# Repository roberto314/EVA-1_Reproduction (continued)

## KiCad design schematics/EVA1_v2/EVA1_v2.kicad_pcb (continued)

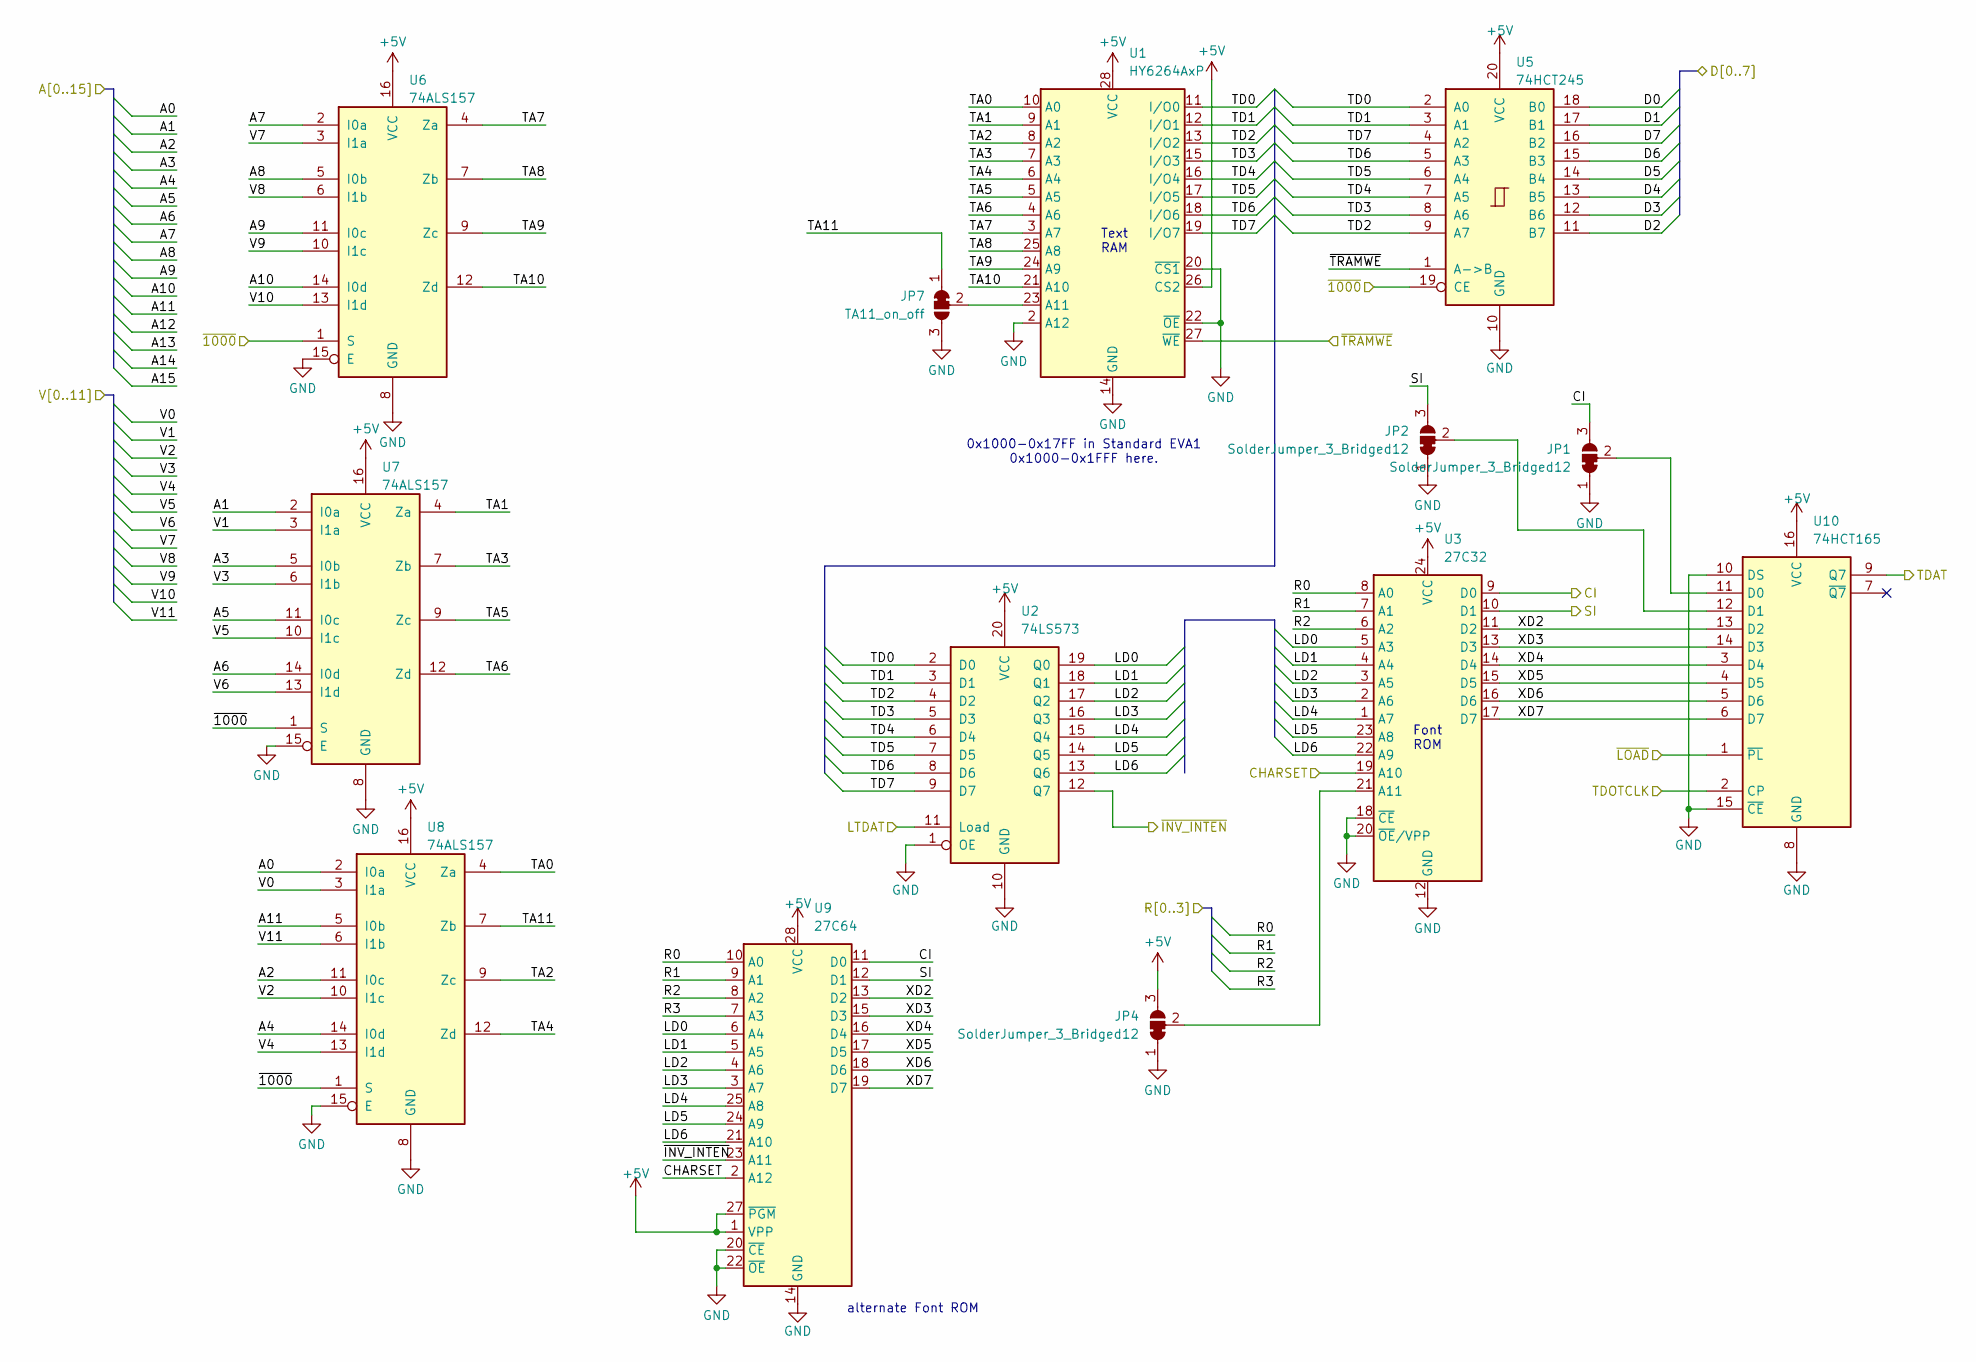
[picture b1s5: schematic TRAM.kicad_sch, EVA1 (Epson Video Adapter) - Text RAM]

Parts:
JP1, JP2, JP4: SolderJumper_3_Bridged12; SolderJumper-3_P1.3mm_Bridged12_RoundedPad1.0x1.5mm
JP7: TA11_on_off; SolderJumper-3_P1.3mm_Bridged12_RoundedPad1.0x1.5mm
U1: HY6264AxP; DIP-28_W15.24mm
U2: 74LS573; DIP-20_W7.62mm
U3: 27C32; DIP-24_W15.24mm
U5: 74HCT245; DIP-20_W7.62mm
U6, U7, U8: 74ALS157; DIP-16_W7.62mm
U9: 27C64; DIP-28_W15.24mm
U10: 74HCT165; DIP-16_W7.62mm_Socket

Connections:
+5V: JP4.3 (B), U1.26 (CS2), U1.28 (VCC), U2.20 (VCC), U3.24 (VCC), U5.20 (VCC), U6.16 (VCC), U7.16 (VCC), U8.16 (VCC), U9.1 (VPP), U9.27 (~PGM), U9.28 (VCC), U10.16 (VCC); also elsewhere on the board
/A0: U8.2 (I0a); also elsewhere on the board
/A1: U7.2 (I0a); also elsewhere on the board
/A2: U8.11 (I0c); also elsewhere on the board
/A3: U7.5 (I0b); also elsewhere on the board
/A4: U8.14 (I0d); also elsewhere on the board
/A5: U7.11 (I0c); also elsewhere on the board
/A6: U7.14 (I0d); also elsewhere on the board
/A7: U6.2 (I0a); also elsewhere on the board
/A8: U6.5 (I0b); also elsewhere on the board
/A9: U6.11 (I0c); also elsewhere on the board
/A10: U6.14 (I0d); also elsewhere on the board
/A11: U8.5 (I0b); also elsewhere on the board
/CHARSET: U3.19 (A10), U9.2 (A12); also elsewhere on the board
/CI: JP1.3 (B), U3.9 (D0), U9.11 (D0)
/D0: U5.18 (B0); also elsewhere on the board
/D1: U5.17 (B1); also elsewhere on the board
/D2: U5.11 (B7); also elsewhere on the board
/D3: U5.12 (B6); also elsewhere on the board
/D4: U5.13 (B5); also elsewhere on the board
/D5: U5.14 (B4); also elsewhere on the board
/D6: U5.15 (B3); also elsewhere on the board
/D7: U5.16 (B2); also elsewhere on the board
/LTDAT: U2.11 (Load); also elsewhere on the board
/R0: U3.8 (A0), U9.10 (A0); also elsewhere on the board
/R1: U3.7 (A1), U9.9 (A1); also elsewhere on the board
/R2: U3.6 (A2), U9.8 (A2); also elsewhere on the board
/R3: U9.7 (A3); also elsewhere on the board
/SI: JP2.3 (B), U3.10 (D1), U9.12 (D1)
/TDAT: U10.9 (Q7); also elsewhere on the board
/TDOTCLK: U10.2 (CP); also elsewhere on the board
/Text RAM, MUX and Shiftregister1/LD0: U2.19 (Q0), U3.5 (A3), U9.6 (A4)
/Text RAM, MUX and Shiftregister1/LD1: U2.18 (Q1), U3.4 (A4), U9.5 (A5)
/Text RAM, MUX and Shiftregister1/LD2: U2.17 (Q2), U3.3 (A5), U9.4 (A6)
/Text RAM, MUX and Shiftregister1/LD3: U2.16 (Q3), U3.2 (A6), U9.3 (A7)
/Text RAM, MUX and Shiftregister1/LD4: U2.15 (Q4), U3.1 (A7), U9.25 (A8)
/Text RAM, MUX and Shiftregister1/LD5: U2.14 (Q5), U3.23 (A8), U9.24 (A9)
/Text RAM, MUX and Shiftregister1/LD6: U2.13 (Q6), U3.22 (A9), U9.21 (A10)
/Text RAM, MUX and Shiftregister1/TA0: U1.10 (A0), U8.4 (Za)
/Text RAM, MUX and Shiftregister1/TA1: U1.9 (A1), U7.4 (Za)
/Text RAM, MUX and Shiftregister1/TA2: U1.8 (A2), U8.9 (Zc)
/Text RAM, MUX and Shiftregister1/TA3: U1.7 (A3), U7.7 (Zb)
/Text RAM, MUX and Shiftregister1/TA4: U1.6 (A4), U8.12 (Zd)
/Text RAM, MUX and Shiftregister1/TA5: U1.5 (A5), U7.9 (Zc)
/Text RAM, MUX and Shiftregister1/TA6: U1.4 (A6), U7.12 (Zd)
/Text RAM, MUX and Shiftregister1/TA7: U1.3 (A7), U6.4 (Za)
/Text RAM, MUX and Shiftregister1/TA8: U1.25 (A8), U6.7 (Zb)
/Text RAM, MUX and Shiftregister1/TA9: U1.24 (A9), U6.9 (Zc)
/Text RAM, MUX and Shiftregister1/TA10: U1.21 (A10), U6.12 (Zd)
/Text RAM, MUX and Shiftregister1/TA11: JP7.1 (A), U8.7 (Zb)
/Text RAM, MUX and Shiftregister1/TD0: U1.11 (I/O0), U2.2 (D0), U5.2 (A0)
/Text RAM, MUX and Shiftregister1/TD1: U1.12 (I/O1), U2.3 (D1), U5.3 (A1)
/Text RAM, MUX and Shiftregister1/TD2: U1.13 (I/O2), U2.4 (D2), U5.9 (A7)
/Text RAM, MUX and Shiftregister1/TD3: U1.15 (I/O3), U2.5 (D3), U5.8 (A6)
/Text RAM, MUX and Shiftregister1/TD4: U1.16 (I/O4), U2.6 (D4), U5.7 (A5)
/Text RAM, MUX and Shiftregister1/TD5: U1.17 (I/O5), U2.7 (D5), U5.6 (A4)
/Text RAM, MUX and Shiftregister1/TD6: U1.18 (I/O6), U2.8 (D6), U5.5 (A3)
/Text RAM, MUX and Shiftregister1/TD7: U1.19 (I/O7), U2.9 (D7), U5.4 (A2)
/Text RAM, MUX and Shiftregister1/XD2: U3.11 (D2), U9.13 (D2), U10.13 (D2)
/Text RAM, MUX and Shiftregister1/XD3: U3.13 (D3), U9.15 (D3), U10.14 (D3)
/Text RAM, MUX and Shiftregister1/XD4: U3.14 (D4), U9.16 (D4), U10.3 (D4)
/Text RAM, MUX and Shiftregister1/XD5: U3.15 (D5), U9.17 (D5), U10.4 (D5)
/Text RAM, MUX and Shiftregister1/XD6: U3.16 (D6), U9.18 (D6), U10.5 (D6)
/Text RAM, MUX and Shiftregister1/XD7: U3.17 (D7), U9.19 (D7), U10.6 (D7)
/Text RAM, MUX and Shiftregister1/~INV_INTEN: U2.12 (Q7), U9.23 (A11); also elsewhere on the board
/V0: U8.3 (I1a); also elsewhere on the board
/V1: U7.3 (I1a); also elsewhere on the board
/V2: U8.10 (I1c); also elsewhere on the board
/V3: U7.6 (I1b); also elsewhere on the board
/V4: U8.13 (I1d); also elsewhere on the board
/V5: U7.10 (I1c); also elsewhere on the board
/V6: U7.13 (I1d); also elsewhere on the board
/V7: U6.3 (I1a); also elsewhere on the board
/V8: U6.6 (I1b); also elsewhere on the board
/V9: U6.10 (I1c); also elsewhere on the board
/V10: U6.13 (I1d); also elsewhere on the board
/V11: U8.6 (I1b); also elsewhere on the board
/~1000: U5.19 (CE), U6.1 (S), U7.1 (S), U8.1 (S); also elsewhere on the board
/~LOAD: U10.1 (~PL); also elsewhere on the board
/~TRAMWE: U1.27 (~WE), U5.1 (A->B); also elsewhere on the board
GND: JP1.1 (A), JP2.1 (A), JP4.1 (A), JP7.3 (B), U1.2 (A12), U1.14 (GND), U1.20 (~CS1), U1.22 (~OE), U2.1 (OE), U2.10 (GND), U3.12 (GND), U3.18 (~CE), U3.20 (~OE/VPP), U5.10 (GND), U6.8 (GND), U6.15 (E), U7.8 (GND), U7.15 (E), U8.8 (GND), U8.15 (E), U9.14 (GND), U9.20 (~CE), U9.22 (~OE), U10.8 (GND), U10.10 (DS), U10.15 (~CE); also elsewhere on the board
unnamed: JP1.2 (C), U10.11 (D0)
unnamed: JP2.2 (C), U10.12 (D1)
unnamed: JP4.2 (C), U3.21 (A11)
unnamed: JP7.2 (C), U1.23 (A11)

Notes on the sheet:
0x1000-0x17FF in Standard EVA1 0x1000-0x1FFF here.
Font ROM
Text RAM
alternate Font ROM

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
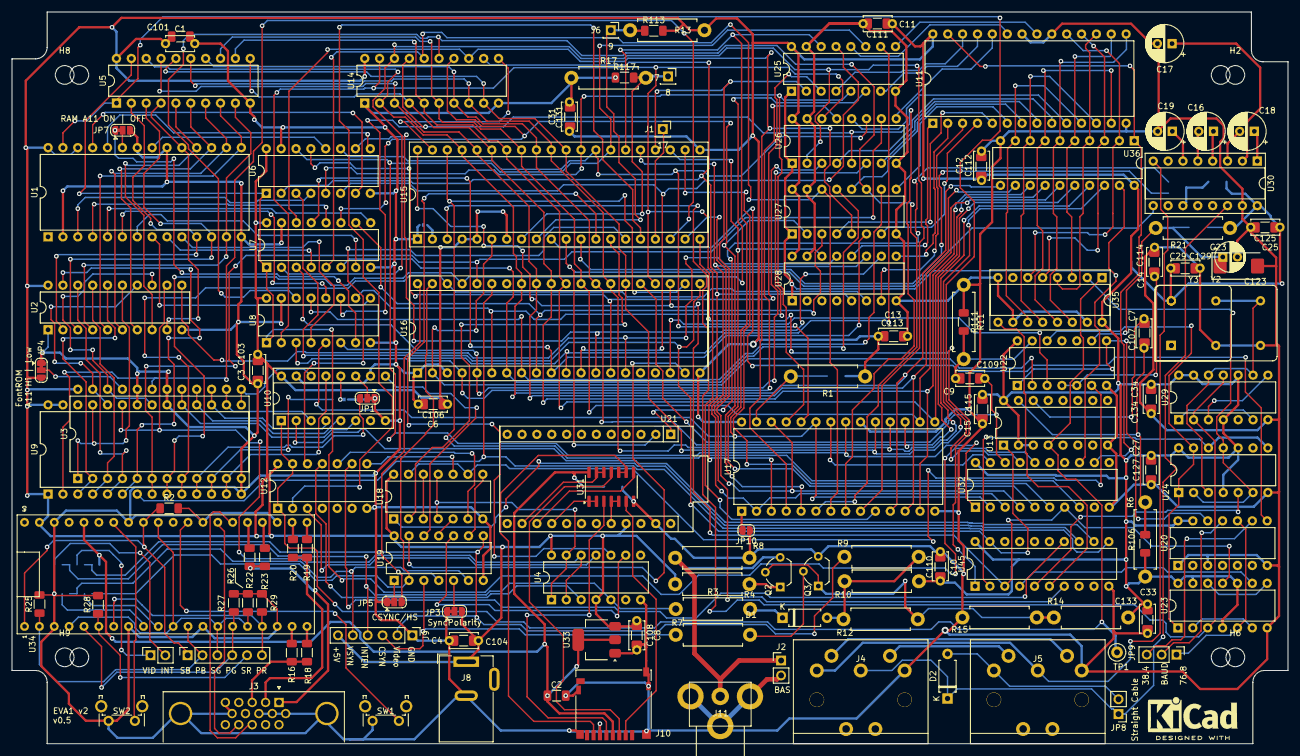
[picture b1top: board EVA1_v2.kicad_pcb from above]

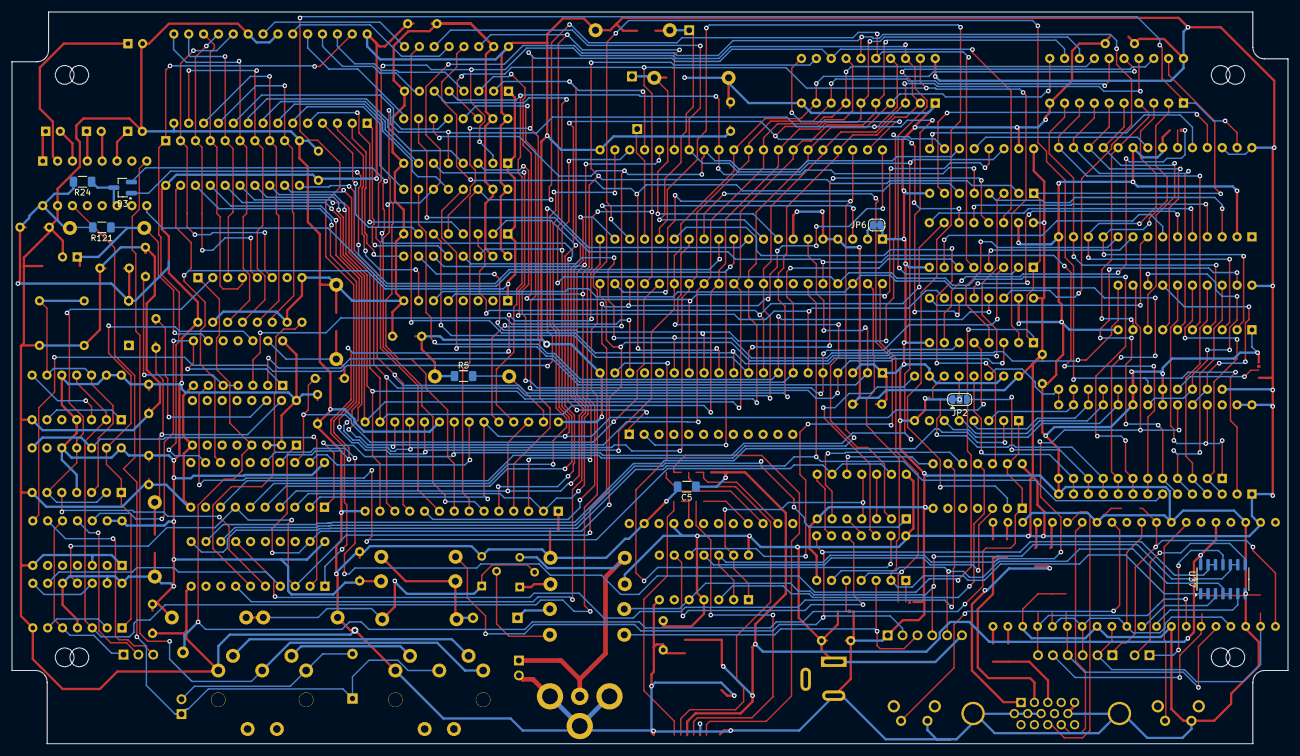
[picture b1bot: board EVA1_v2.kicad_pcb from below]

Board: 2 copper layers, 218.0 x 125.0 mm, 160 parts (8 on the bottom side), 229 nets.

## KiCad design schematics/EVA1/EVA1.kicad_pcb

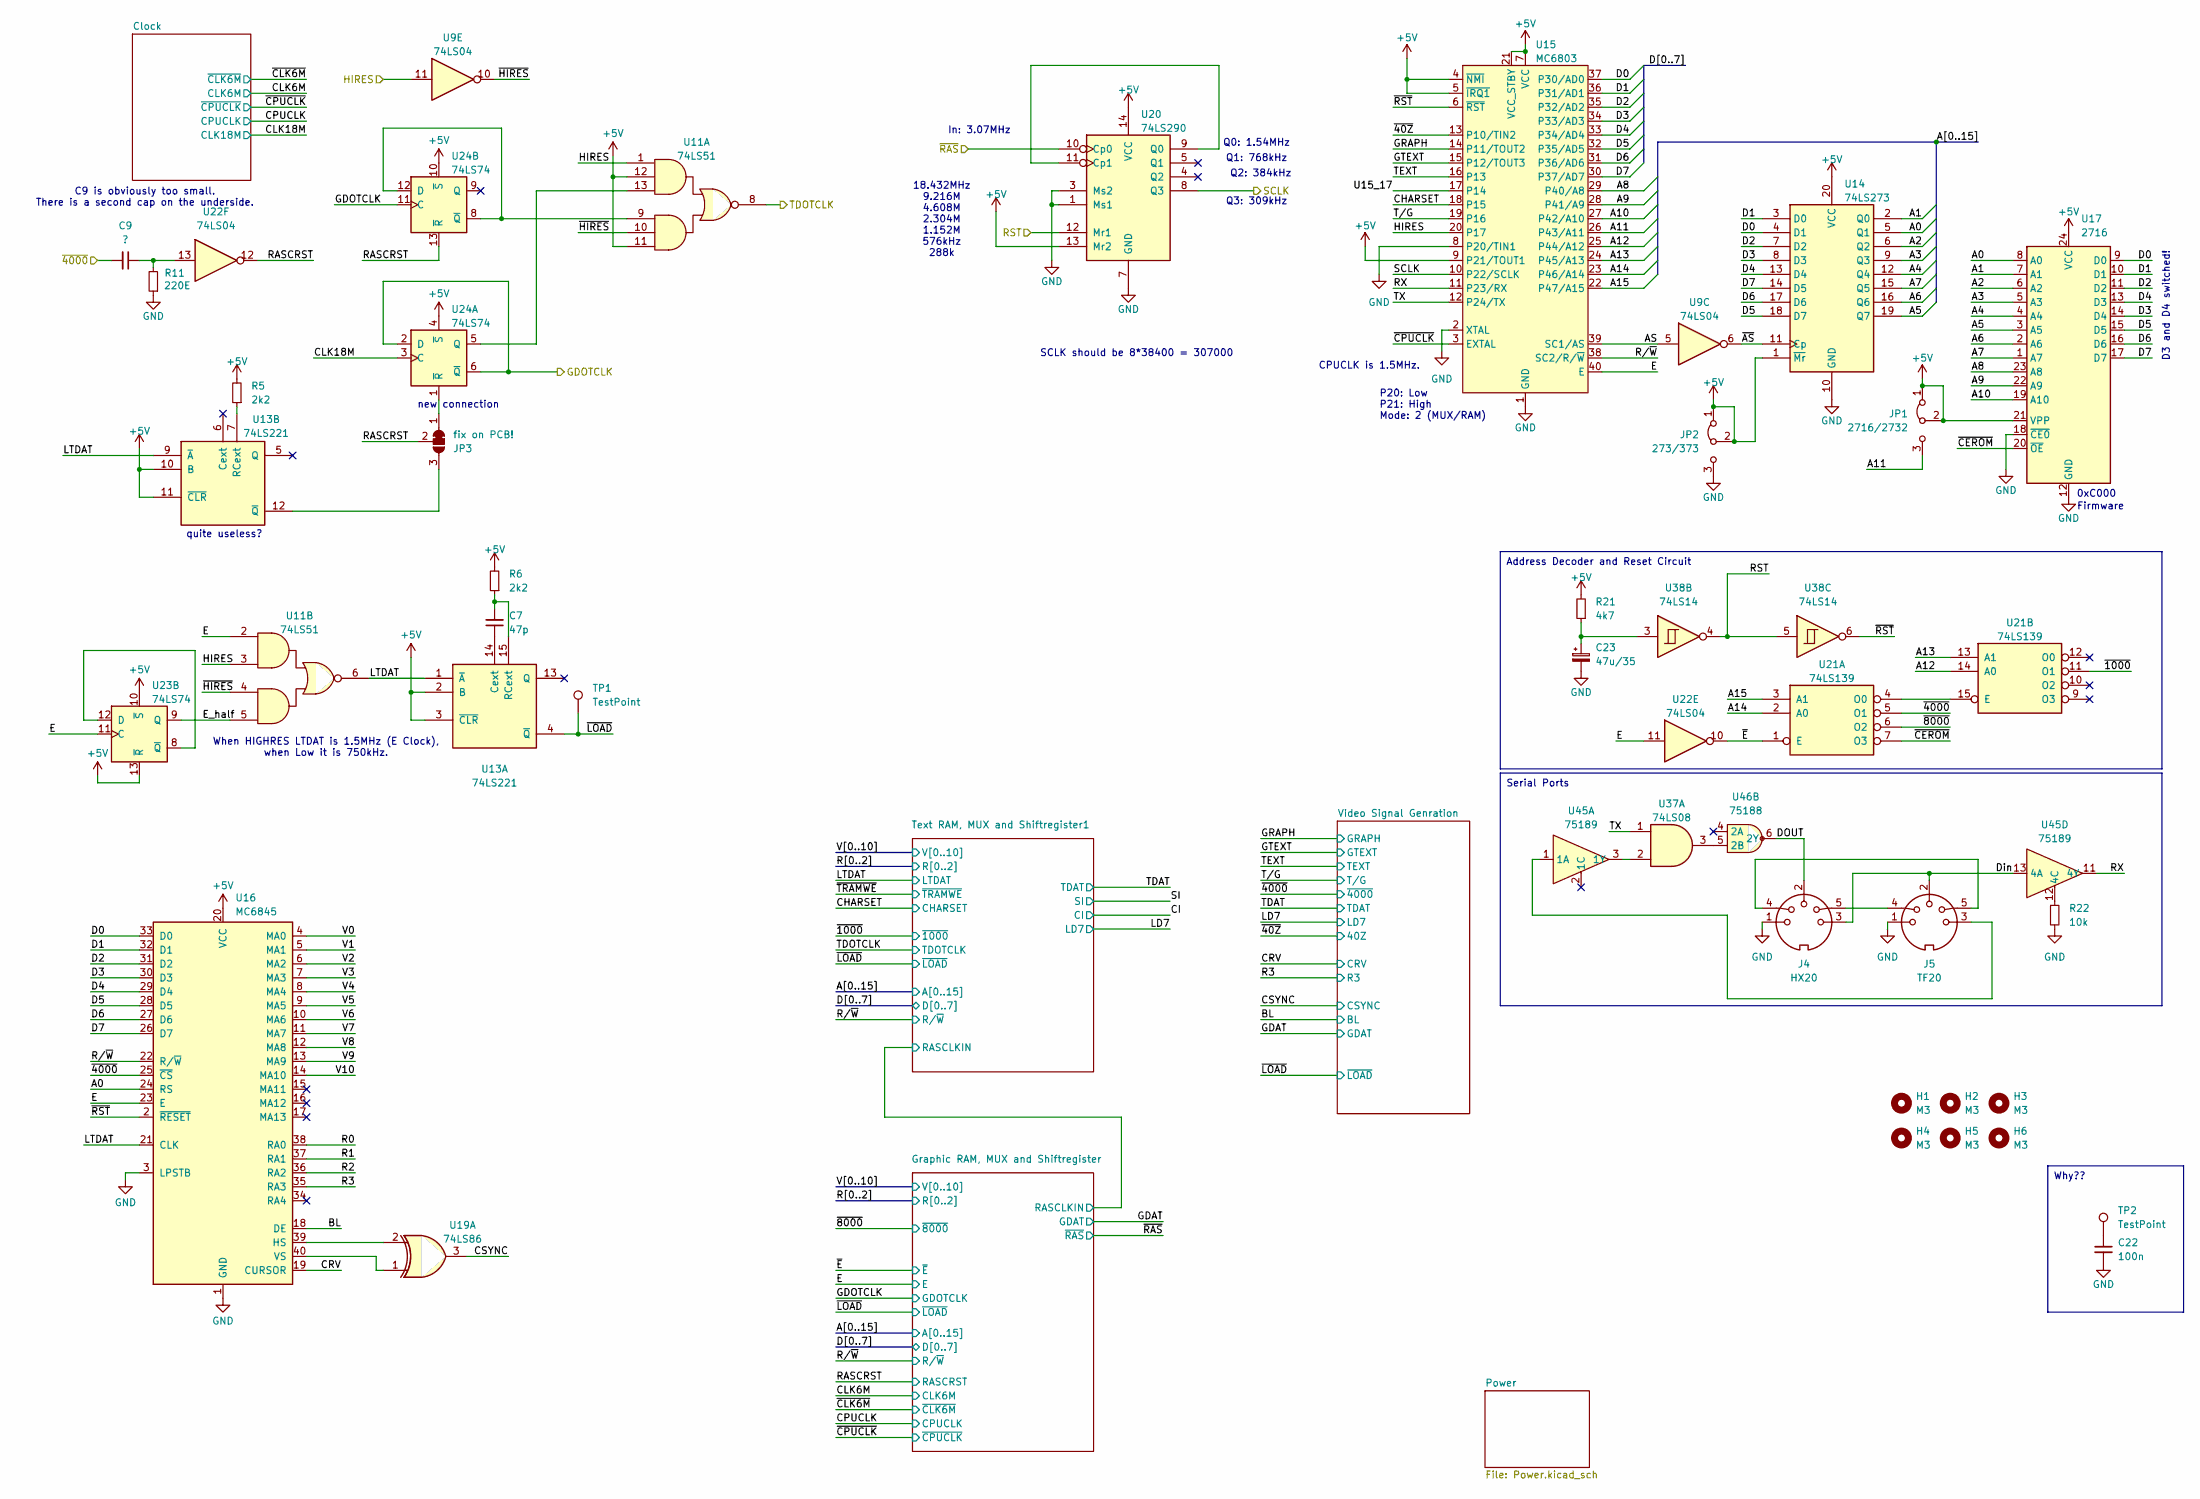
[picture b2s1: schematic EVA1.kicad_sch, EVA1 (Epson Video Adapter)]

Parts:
C7: 47p; C_Disc_D4.7mm_W2.5mm_P5.00mm
C9: ?; C_Disc_D4.7mm_W2.5mm_P5.00mm
C22: 100n; C_Disc_D4.7mm_W2.5mm_P5.00mm
C23: 47u/35; CP_Radial_D5.0mm_P2.50mm
H1, H2, H3, H4, H5, H6: M3; MountingHole_3.2mm_M3
J4: HX20; DIN-5_Stereo
J5: TF20; DIN-5_Stereo
JP1: 2716/2732; PinHeader_1x03_P2.54mm_Vertical
JP2: 273/373; PinHeader_1x03_P2.54mm_Vertical
JP3: fix on PCB!; SolderJumper-3_P1.3mm_Bridged12_RoundedPad1.0x1.5mm
R5, R6: 2k2; R_Axial_DIN0411_L9.9mm_D3.6mm_P12.70mm_Horizontal
R11: 220E; R_Axial_DIN0411_L9.9mm_D3.6mm_P12.70mm_Horizontal
R21: 4k7; R_Axial_DIN0411_L9.9mm_D3.6mm_P12.70mm_Horizontal
R22: 10k; R_Axial_DIN0411_L9.9mm_D3.6mm_P12.70mm_Horizontal
TP1, TP2: TestPoint; TestPoint_Loop_D1.80mm_Drill1.0mm_Beaded
U9, U22: 74LS04; DIP-14_W7.62mm
U11: 74LS51; DIP-14_W7.62mm
U13: 74LS221; DIP-16_W7.62mm
U14: 74LS273; DIP-20_W7.62mm
U15: MC6803; DIP-40_W15.24mm_Socket
U16: MC6845; DIP-40_W15.24mm_Socket
U17: 2716; DIP-24_W15.24mm
U19: 74LS86; DIP-14_W7.62mm
U20: 74LS290; DIP-14_W7.62mm
U21: 74LS139; DIP-16_W7.62mm
U23, U24: 74LS74; DIP-14_W7.62mm
U37: 74LS08; DIP-14_W7.62mm
U38: 74LS14; DIP-14_W7.62mm
U45: 75189; DIP-14_W7.62mm
U46: 75188; DIP-14_W7.62mm

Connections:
+5V: JP1.1 (A), JP1.2 (C), JP2.1 (A), JP2.2 (C), R5.2, R6.2, R21.2, U11.11, U11.12, U13.2 (B), U13.3 (~CLR), U13.10 (B), U13.11 (~CLR), U14.1 (~Mr), U14.20 (VCC), U15.4 (~NMI), U15.5 (~IRQ1), U15.7 (VCC), U15.9 (P21/TOUT1), U15.21 (VCC_STBY), U16.20 (VCC), U17.21 (VPP), U17.24 (VCC), U20.13 (Mr2), U20.14 (VCC), U23.10 (~S), U23.13 (~R), U24.4 (~S), U24.10 (~S); also elsewhere on the board
/A0: U14.5 (Q1), U16.24 (RS), U17.8 (A0); also elsewhere on the board
/A1: U14.2 (Q0), U17.7 (A1); also elsewhere on the board
/A2: U14.6 (Q2), U17.6 (A2); also elsewhere on the board
/A3: U14.9 (Q3), U17.5 (A3); also elsewhere on the board
/A4: U14.12 (Q4), U17.4 (A4); also elsewhere on the board
/A5: U14.19 (Q7), U17.3 (A5); also elsewhere on the board
/A6: U14.16 (Q6), U17.2 (A6); also elsewhere on the board
/A7: U14.15 (Q5), U17.1 (A7); also elsewhere on the board
/A8: U15.29 (P40/A8), U17.23 (A8); also elsewhere on the board
/A9: U15.28 (P41/A9), U17.22 (A9); also elsewhere on the board
/A10: U15.27 (P42/A10), U17.19 (A10); also elsewhere on the board
/A11: JP1.3 (B), U15.26 (P43/A11); also elsewhere on the board
/A12: U15.25 (P44/A12), U21.14 (A0); also elsewhere on the board
/A13: U15.24 (P45/A13), U21.13 (A1); also elsewhere on the board
/A14: U15.23 (P46/A14), U21.2 (A0)
/A15: U15.22 (P47/A15), U21.3 (A1)
/AS: U9.5, U15.39 (SC1/AS)
/BL: U16.18 (DE); also elsewhere on the board
/CHARSET: U15.18 (P15); also elsewhere on the board
/CLK18M: U24.3 (C); also elsewhere on the board
/CRV: U16.19 (CURSOR); also elsewhere on the board
/D0: U14.4 (D1), U15.37 (P30/AD0), U16.33 (D0), U17.9 (D0); also elsewhere on the board
/D1: U14.3 (D0), U15.36 (P31/AD1), U16.32 (D1), U17.10 (D1); also elsewhere on the board
/D2: U14.7 (D2), U15.35 (P32/AD2), U16.31 (D2), U17.11 (D2); also elsewhere on the board
/D3: U14.8 (D3), U15.34 (P33/AD3), U16.30 (D3), U17.14 (D4); also elsewhere on the board
/D4: U14.13 (D4), U15.33 (P34/AD4), U16.29 (D4), U17.13 (D3); also elsewhere on the board
/D5: U14.18 (D7), U15.32 (P35/AD5), U16.28 (D5), U17.15 (D5); also elsewhere on the board
/D6: U14.17 (D6), U15.31 (P36/AD6), U16.27 (D6), U17.16 (D6); also elsewhere on the board
/D7: U14.14 (D5), U15.30 (P37/AD7), U16.26 (D7), U17.17 (D7); also elsewhere on the board
/DOUT: J4.2, U46.6 (2Y)
/Din: J4.3, J5.2, U45.13 (4A)
/E: U11.2, U15.40 (E), U16.23 (E), U22.11, U23.11 (C); also elsewhere on the board
/E_half: U11.5, U23.9 (Q)
/GDOTCLK: U24.2 (D), U24.6 (~Q), U24.11 (C); also elsewhere on the board
/GRAPH: U15.14 (P11/TOUT2); also elsewhere on the board
/GTEXT: U15.15 (P12/TOUT3); also elsewhere on the board
/HIRES: U9.11, U11.1, U11.3, U15.20 (P17)
/HS: U16.39 (HS), U19.2
/LTDAT: U11.6, U13.1 (~A), U13.9 (~A), U16.21 (CLK); also elsewhere on the board
/R0: U16.38 (RA0); also elsewhere on the board
/R1: U16.37 (RA1); also elsewhere on the board
/R2: U16.36 (RA2); also elsewhere on the board
/R3: U16.35 (RA3); also elsewhere on the board
/RASCRST: JP3.2 (C), U22.12, U24.13 (~R); also elsewhere on the board
/RST: U20.12 (Mr1), U38.4, U38.5
/RX: U15.11 (P23/RX), U45.11 (4Y)
/R/~W: U15.38 (SC2/R/~W), U16.22 (R/~W); also elsewhere on the board
/SCLK: U15.10 (P22/SCLK), U20.8 (Q3)
/TDOTCLK: U11.8; also elsewhere on the board
/TEXT: U15.16 (P13); also elsewhere on the board
/TX: U15.12 (P24/TX), U37.1
/T/G: U15.19 (P16); also elsewhere on the board
/U15_17: U15.17 (P14)
/V0: U16.4 (MA0); also elsewhere on the board
/V1: U16.5 (MA1); also elsewhere on the board
/V2: U16.6 (MA2); also elsewhere on the board
/V3: U16.7 (MA3); also elsewhere on the board
/V4: U16.8 (MA4); also elsewhere on the board
/V5: U16.9 (MA5); also elsewhere on the board
/V6: U16.10 (MA6); also elsewhere on the board
/V7: U16.11 (MA7); also elsewhere on the board
/V8: U16.12 (MA8); also elsewhere on the board
/V9: U16.13 (MA9); also elsewhere on the board
/V10: U16.14 (MA10); also elsewhere on the board
/VS: U16.40 (VS), U19.1
/~40Z: U15.13 (P10/TIN2); also elsewhere on the board
/~1000: U21.11 (O1); also elsewhere on the board
/~4000: C9.2, U16.25 (~CS), U21.5 (O1)
/~8000: U21.6 (O2); also elsewhere on the board
/~AS: U9.6, U14.11 (Cp)
/~CEROM: U17.20 (~OE), U21.7 (O3)
/~CPUCLK: U15.3 (EXTAL); also elsewhere on the board
/~E: U21.1 (E), U22.10; also elsewhere on the board
/~HIRES: U9.10, U11.4, U11.10
/~LOAD: TP1.1, U13.4 (~Q); also elsewhere on the board
/~RAS: U20.10 (Cp0); also elsewhere on the board
/~RST: U15.6 (~RST), U16.2 (~RESET), U38.6
GND: C22.2, C23.2, J4.1, J5.1, JP2.3 (B), R11.1, R22.2, U14.10 (GND), U15.1 (GND), U15.2 (XTAL), U15.8 (P20/TIN1), U16.1 (GND), U16.3 (LPSTB), U17.12 (GND), U17.18 (~CE0), U20.1 (Ms1), U20.3 (Ms2), U20.7 (GND); also elsewhere on the board
unnamed: C9.1, R11.2, U22.13
unnamed: C22.1, TP2.1
unnamed: C23.1, R21.1, U38.3
unnamed: J4.4, J5.5
unnamed: J4.5, J5.4
unnamed: JP3.1 (A), U24.1 (~R)
unnamed: JP3.3 (B), U13.12 (~Q)
unnamed 172: U19.3; also elsewhere on the board
unnamed: C7.1, U13.14 (Cext)
unnamed: C7.2, R6.1, U13.15 (RCext)
unnamed: R5.1, U13.7 (RCext)
unnamed: U20.9 (Q0), U20.11 (Cp1)
unnamed: U21.4 (O0), U21.15 (E)
unnamed: U23.8 (~Q), U23.12 (D)
unnamed: U11.13, U24.5 (Q)
unnamed: U11.9, U24.8 (~Q), U24.12 (D)
unnamed: J5.3, U45.1 (1A)
unnamed: U37.2, U45.3 (1Y)
unnamed: R22.1, U45.12 (4C)
unnamed: U37.3, U46.5 (2B)

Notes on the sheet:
Address Decoder and Reset Circuit
Serial Ports
Why??
quite useless?
P20: Low P21: High Mode: 2 (MUX/RAM)
C9 is obviously too small. There is a second cap on the underside.
Q1: 768kHz
CPUCLK is 1.5MHz.
D3 and D4 switched!
Q3: 309kHz
SCLK should be 8*38400 = 307000
When HIGHRES LTDAT is 1.5MHz (E Clock), when Low it is 750kHz.
Firmware
18.432MHz 9.216M 4.608M 2.304M 1.152M 576kHz 288k
new connection
0xC000
Q0: 1.54MHz
In: 3.07MHz
Q2: 384kHz

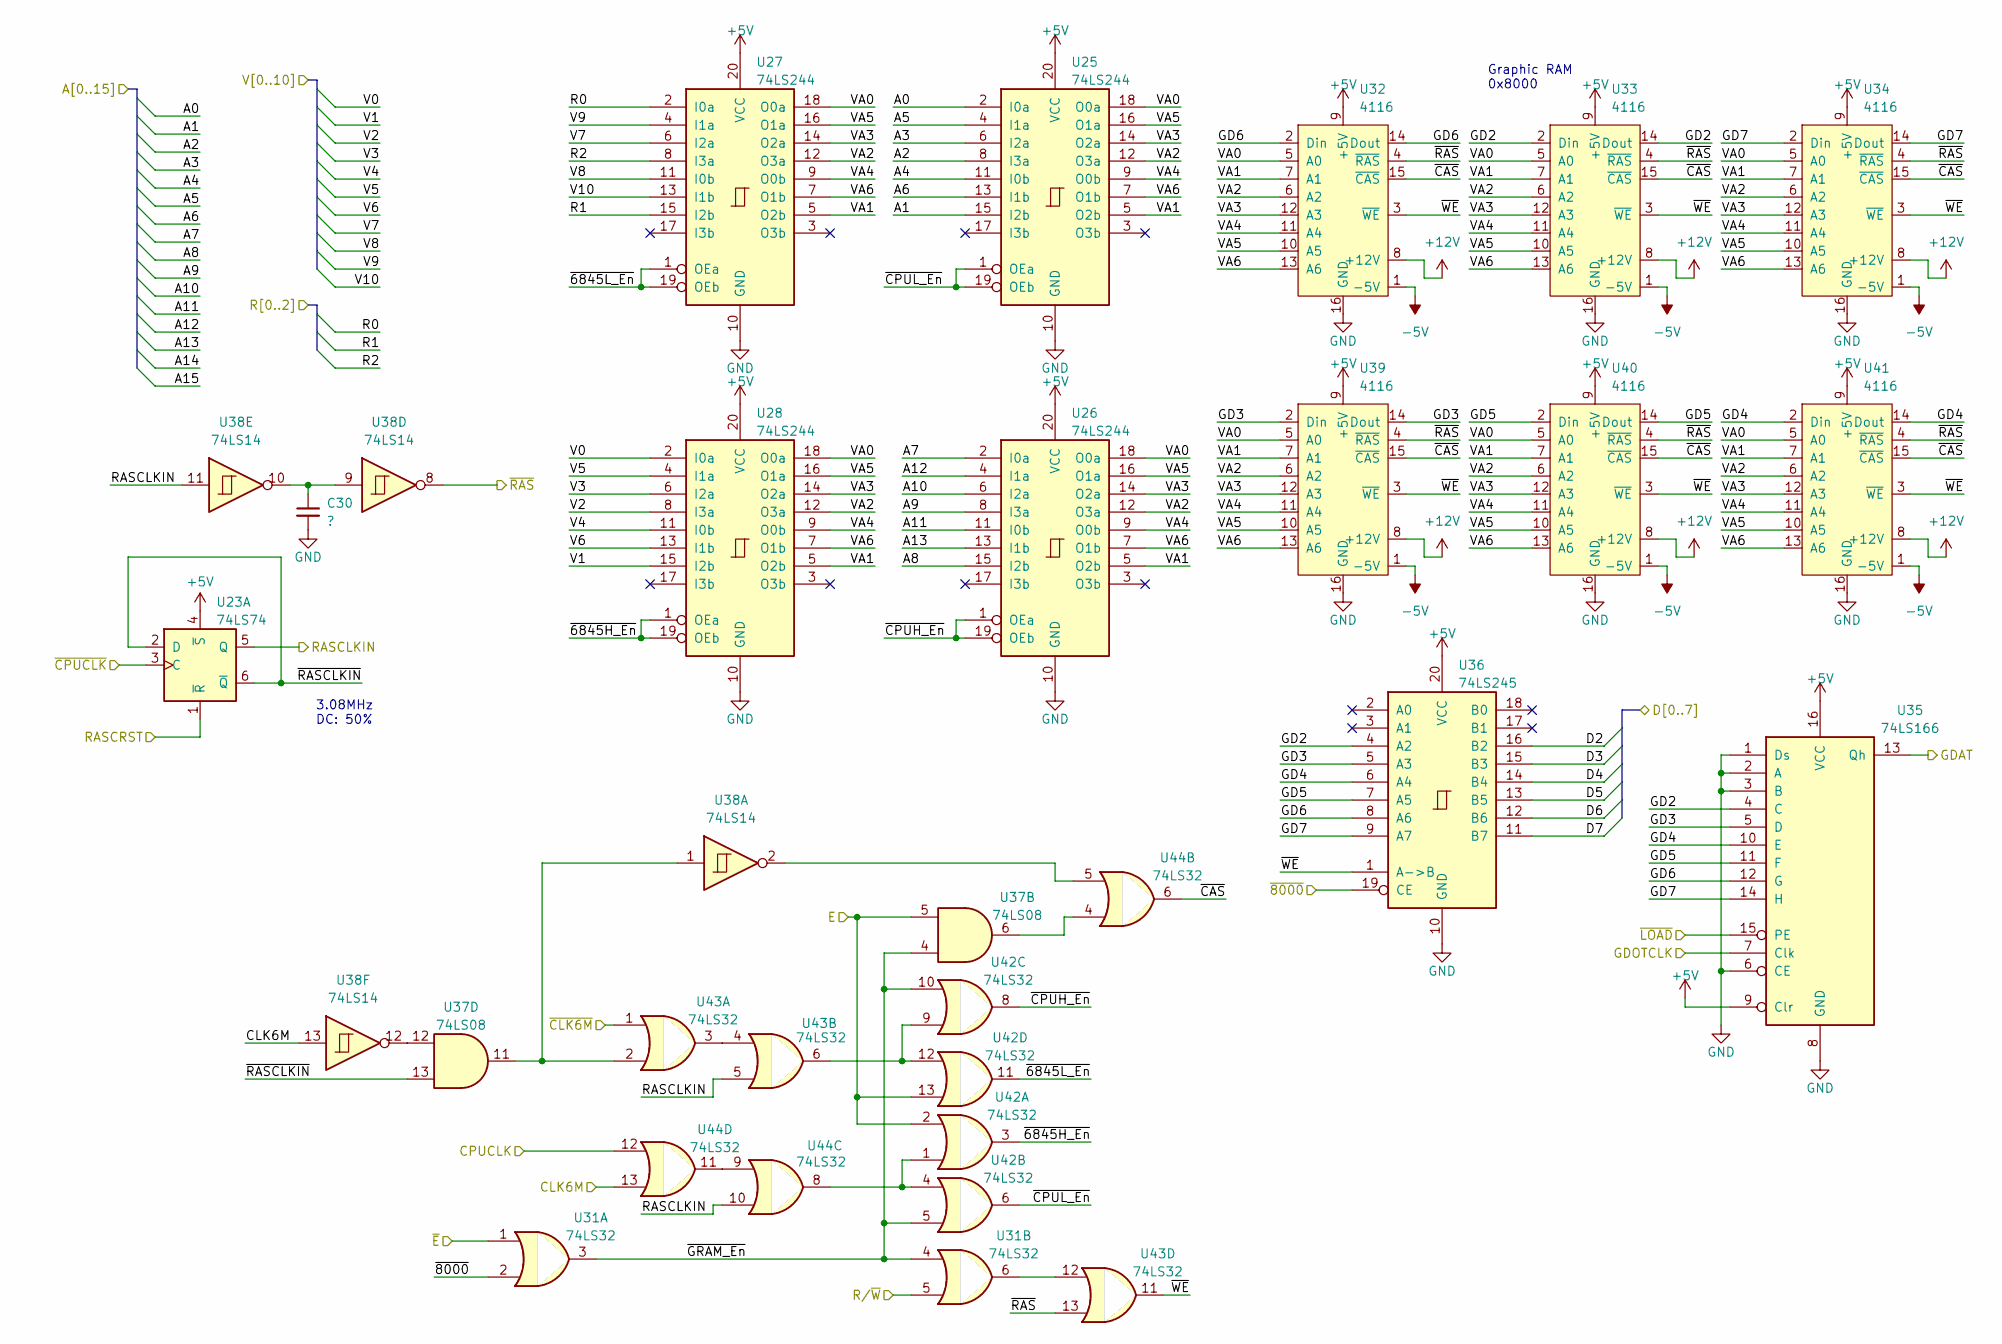
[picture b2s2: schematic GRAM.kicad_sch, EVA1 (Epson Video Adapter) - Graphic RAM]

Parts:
C30: ?; C_Disc_D4.7mm_W2.5mm_P5.00mm
U23: 74LS74; DIP-14_W7.62mm
U25, U26, U27, U28: 74LS244; DIP-20_W7.62mm
U31, U42, U43, U44: 74LS32; DIP-14_W7.62mm
U32, U33, U34, U39, U40, U41: 4116; DIP-16_W7.62mm
U35: 74LS166; DIP-16_W7.62mm
U36: 74LS245; DIP-20_W7.62mm
U37: 74LS08; DIP-14_W7.62mm
U38: 74LS14; DIP-14_W7.62mm

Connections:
+5V: U23.4 (~S), U25.20 (VCC), U26.20 (VCC), U27.20 (VCC), U28.20 (VCC), U32.9 (+5V), U33.9 (+5V), U34.9 (+5V), U35.9 (Clr), U35.16 (VCC), U36.20 (VCC), U39.9 (+5V), U40.9 (+5V), U41.9 (+5V); also elsewhere on the board
+12V: U32.8 (+12V), U33.8 (+12V), U34.8 (+12V), U39.8 (+12V), U40.8 (+12V), U41.8 (+12V); also elsewhere on the board
-5V: U32.1 (-5V), U33.1 (-5V), U34.1 (-5V), U39.1 (-5V), U40.1 (-5V), U41.1 (-5V); also elsewhere on the board
/A0: U25.2 (I0a); also elsewhere on the board
/A1: U25.15 (I2b); also elsewhere on the board
/A2: U25.8 (I3a); also elsewhere on the board
/A3: U25.6 (I2a); also elsewhere on the board
/A4: U25.11 (I0b); also elsewhere on the board
/A5: U25.4 (I1a); also elsewhere on the board
/A6: U25.13 (I1b); also elsewhere on the board
/A7: U26.2 (I0a); also elsewhere on the board
/A8: U26.15 (I2b); also elsewhere on the board
/A9: U26.8 (I3a); also elsewhere on the board
/A10: U26.6 (I2a); also elsewhere on the board
/A11: U26.11 (I0b); also elsewhere on the board
/A12: U26.4 (I1a); also elsewhere on the board
/A13: U26.13 (I1b); also elsewhere on the board
/CLK6M: U38.13, U44.13; also elsewhere on the board
/CPUCLK: U44.12; also elsewhere on the board
/D2: U36.16 (B2); also elsewhere on the board
/D3: U36.15 (B3); also elsewhere on the board
/D4: U36.14 (B4); also elsewhere on the board
/D5: U36.13 (B5); also elsewhere on the board
/D6: U36.12 (B6); also elsewhere on the board
/D7: U36.11 (B7); also elsewhere on the board
/E: U37.5, U42.2, U42.13; also elsewhere on the board
/GDAT: U35.13 (Qh); also elsewhere on the board
/GDOTCLK: U35.7 (Clk); also elsewhere on the board
/Graphic RAM, MUX and Shiftregister/GD2: U33.2 (Din), U33.14 (Dout), U35.4 (C), U36.4 (A2)
/Graphic RAM, MUX and Shiftregister/GD3: U35.5 (D), U36.5 (A3), U39.2 (Din), U39.14 (Dout)
/Graphic RAM, MUX and Shiftregister/GD4: U35.10 (E), U36.6 (A4), U41.2 (Din), U41.14 (Dout)
/Graphic RAM, MUX and Shiftregister/GD5: U35.11 (F), U36.7 (A5), U40.2 (Din), U40.14 (Dout)
/Graphic RAM, MUX and Shiftregister/GD6: U32.2 (Din), U32.14 (Dout), U35.12 (G), U36.8 (A6)
/Graphic RAM, MUX and Shiftregister/GD7: U34.2 (Din), U34.14 (Dout), U35.14 (H), U36.9 (A7)
/Graphic RAM, MUX and Shiftregister/RASCLKIN: U23.5 (Q), U38.11, U43.5, U44.10; also elsewhere on the board
/Graphic RAM, MUX and Shiftregister/VA0: U25.18 (O0a), U26.18 (O0a), U27.18 (O0a), U28.18 (O0a), U32.5 (A0), U33.5 (A0), U34.5 (A0), U39.5 (A0), U40.5 (A0), U41.5 (A0)
/Graphic RAM, MUX and Shiftregister/VA1: U25.5 (O2b), U26.5 (O2b), U27.5 (O2b), U28.5 (O2b), U32.7 (A1), U33.7 (A1), U34.7 (A1), U39.7 (A1), U40.7 (A1), U41.7 (A1)
/Graphic RAM, MUX and Shiftregister/VA2: U25.12 (O3a), U26.12 (O3a), U27.12 (O3a), U28.12 (O3a), U32.6 (A2), U33.6 (A2), U34.6 (A2), U39.6 (A2), U40.6 (A2), U41.6 (A2)
/Graphic RAM, MUX and Shiftregister/VA3: U25.14 (O2a), U26.14 (O2a), U27.14 (O2a), U28.14 (O2a), U32.12 (A3), U33.12 (A3), U34.12 (A3), U39.12 (A3), U40.12 (A3), U41.12 (A3)
/Graphic RAM, MUX and Shiftregister/VA4: U25.9 (O0b), U26.9 (O0b), U27.9 (O0b), U28.9 (O0b), U32.11 (A4), U33.11 (A4), U34.11 (A4), U39.11 (A4), U40.11 (A4), U41.11 (A4)
/Graphic RAM, MUX and Shiftregister/VA5: U25.16 (O1a), U26.16 (O1a), U27.16 (O1a), U28.16 (O1a), U32.10 (A5), U33.10 (A5), U34.10 (A5), U39.10 (A5), U40.10 (A5), U41.10 (A5)
/Graphic RAM, MUX and Shiftregister/VA6: U25.7 (O1b), U26.7 (O1b), U27.7 (O1b), U28.7 (O1b), U32.13 (A6), U33.13 (A6), U34.13 (A6), U39.13 (A6), U40.13 (A6), U41.13 (A6)
/Graphic RAM, MUX and Shiftregister/~6845H_En: U28.1 (OEa), U28.19 (OEb), U42.3
/Graphic RAM, MUX and Shiftregister/~6845L_En: U27.1 (OEa), U27.19 (OEb), U42.11
/Graphic RAM, MUX and Shiftregister/~CAS: U32.15 (~CAS), U33.15 (~CAS), U34.15 (~CAS), U39.15 (~CAS), U40.15 (~CAS), U41.15 (~CAS), U44.6
/Graphic RAM, MUX and Shiftregister/~CPUH_En: U26.1 (OEa), U26.19 (OEb), U42.8
/Graphic RAM, MUX and Shiftregister/~CPUL_En: U25.1 (OEa), U25.19 (OEb), U42.6
/Graphic RAM, MUX and Shiftregister/~GRAM_En: U31.3, U31.4, U37.4, U42.5, U42.10
/Graphic RAM, MUX and Shiftregister/~RASCLKIN: U23.2 (D), U23.6 (~Q), U37.13
/Graphic RAM, MUX and Shiftregister/~WE: U32.3 (~WE), U33.3 (~WE), U34.3 (~WE), U36.1 (A->B), U39.3 (~WE), U40.3 (~WE), U41.3 (~WE), U43.11
/R0: U27.2 (I0a); also elsewhere on the board
/R1: U27.15 (I2b); also elsewhere on the board
/R2: U27.8 (I3a); also elsewhere on the board
/RASCRST: U23.1 (~R); also elsewhere on the board
/R/~W: U31.5; also elsewhere on the board
/V0: U28.2 (I0a); also elsewhere on the board
/V1: U28.15 (I2b); also elsewhere on the board
/V2: U28.8 (I3a); also elsewhere on the board
/V3: U28.6 (I2a); also elsewhere on the board
/V4: U28.11 (I0b); also elsewhere on the board
/V5: U28.4 (I1a); also elsewhere on the board
/V6: U28.13 (I1b); also elsewhere on the board
/V7: U27.6 (I2a); also elsewhere on the board
/V8: U27.11 (I0b); also elsewhere on the board
/V9: U27.4 (I1a); also elsewhere on the board
/V10: U27.13 (I1b); also elsewhere on the board
/~8000: U31.2, U36.19 (CE); also elsewhere on the board
/~CLK6M: U43.1; also elsewhere on the board
/~CPUCLK: U23.3 (C); also elsewhere on the board
/~E: U31.1; also elsewhere on the board
/~LOAD: U35.15 (PE); also elsewhere on the board
/~RAS: U32.4 (~RAS), U33.4 (~RAS), U34.4 (~RAS), U38.8, U39.4 (~RAS), U40.4 (~RAS), U41.4 (~RAS), U43.13; also elsewhere on the board
GND: C30.2, U25.10 (GND), U26.10 (GND), U27.10 (GND), U28.10 (GND), U32.16 (GND), U33.16 (GND), U34.16 (GND), U35.1 (Ds), U35.2 (A), U35.3 (B), U35.6 (CE), U35.8 (GND), U36.10 (GND), U39.16 (GND), U40.16 (GND), U41.16 (GND); also elsewhere on the board
unnamed: C30.1, U38.9, U38.10
unnamed: U31.6, U43.12
unnamed: U37.6, U44.4
unnamed: U37.11, U38.1, U43.2
unnamed: U37.12, U38.12
unnamed: U38.2, U44.5
unnamed: U42.1, U42.4, U44.8
unnamed: U42.9, U42.12, U43.6
unnamed: U43.3, U43.4
unnamed: U44.9, U44.11

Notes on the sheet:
Graphic RAM 0x8000
3.08MHz DC: 50%
